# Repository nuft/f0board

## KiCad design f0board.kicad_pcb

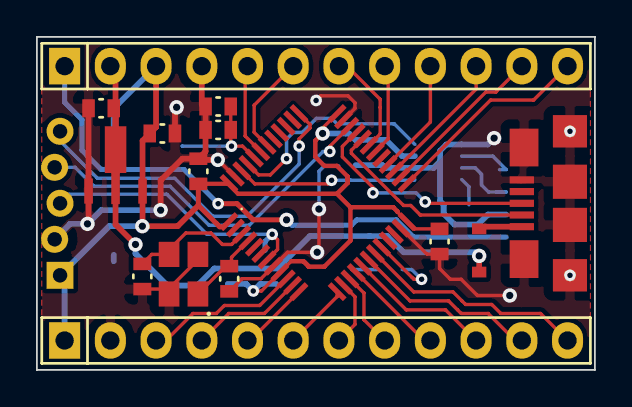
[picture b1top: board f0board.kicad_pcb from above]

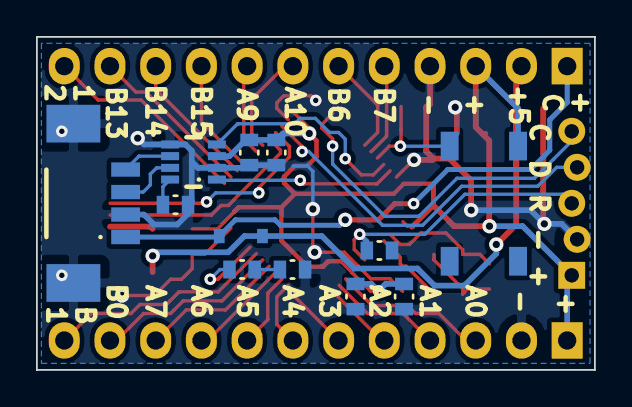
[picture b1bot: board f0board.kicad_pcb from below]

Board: 2 copper layers, 31.0 x 18.5 mm, 28 parts (12 on the bottom side), 38 nets.

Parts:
C1, C3, C4, C5, C7: 100nF; _0603
C2: 4.7uF; _0603
C6, C11, C12: 1uF; _0603
C8: 10nF; _0603
C9, C10: C; _0603
CONN1: SWD; _Pin2mm_5z
CONN2: CAN; _Molex-PicoBlade-SMD-4
CONN3: MICRO_USB; _Micro-USB-AB-receptacle-SMT
D1: LED; _0603
D2, D3: BAT60JFILM; _SOD-323
P1, P2: CONN_12; Pin_Header_Straight_1x12
R1: R; _0603
R2: 10k; _0603
R3: 0; _0603
SW1: SW_PUSH; _PTS525SK15-SMT-Pushbutton
U1: STM32F303CCT6; _LQFP48
U2: MCP1700; _MCP1700-SOT-89
U3: MAX3051; _SOT23-8
X1: XTAL-SMD-4-PADS; _TSX-3225-SMD-XTAL

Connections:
/5V: C11.1, D2.2, D3.2, P1.2, U2.3
/5VCAN: CONN2.1, D3.1, P1.1
/BOOT0: C1.1, R2.1, SW1.1, U1.44
/CAN_RX: U1.45, U3.4
/CAN_TX: U1.46, U3.1
/LED: D1.1, U1.20
/PA0: P2.3, U1.10
/PA1: P2.4, U1.11
/PA2: P2.5, U1.12
/PA3: P2.6, U1.13
/PA4: P2.7, U1.14
/PA5: P2.8, U1.15
/PA6: P2.9, U1.16
/PA7: P2.10, U1.17
/PA9: P1.8, U1.30
/PA10: P1.7, U1.31
/PB0: P2.11, U1.18
/PB1: P2.12, U1.19
/PB6: P1.6, U1.42
/PB7: P1.5, U1.43
/PB12: P1.12, U1.25
/PB13: P1.11, U1.26
/PB14: P1.10, U1.27
/PB15: P1.9, U1.28
/RST: C4.1, CONN1.3, U1.7
/SWDCLK: CONN1.5, U1.37
/SWDIO: CONN1.4, U1.34
/USB_DM: CONN3.2, U1.32
/USB_DP: CONN3.3, U1.33
/VUSB: CONN3.1, D2.1
GND: C1.2, C2.2, C3.2, C4.2, C5.2, C6.2, C7.2, C8.2, C9.2, C10.2, C11.2, C12.2, CONN1.2, CONN2.2, CONN2.MECH, CONN3.5, CONN3.6, P1.4, P2.2, R1.2, R2.2, R3.2, U1.8, U1.23, U1.35, U1.47, U2.1, U3.2, U3.5, X1.2, X1.4
unnamed: C9.1, U1.4, X1.1
unnamed: C10.1, U1.3, X1.3
unnamed: CONN2.3, U3.7
unnamed: CONN2.4, U3.6
unnamed: D1.2, R1.1
unnamed: R3.1, U3.8
VCC: C2.1, C3.1, C5.1, C6.1, C7.1, C8.1, C12.1, CONN1.1, P1.3, P2.1, SW1.2, U1.1, U1.9, U1.24, U1.36, U1.48, U2.2, U3.3

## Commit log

2014-12-07 Initial commit, schematic already done by @Stapelzeiger.
2014-12-07 Add annotation.
2014-12-07 Update lib, change settings.
2014-12-07 Create pcb file, started coarse placing, defined outline.
2014-12-07 Add dimensioning.
2014-12-07 placing/routing, change pinorder, add diode.
2014-12-09 Routing, change LED Pin.
2014-12-09 Change MCP1700 footprint.
2014-12-09 Big layout change, routing almost finished.
2014-12-09 Add missing connection to LED, improved GND and VCC routing.
2014-12-09 Improve GND connection.
2014-12-09 Connect USB shield to GND, update footprints to fix DRC issue.
2014-12-09 Changes at Crystal after review, improved GND connection.
2014-12-10 Additional GND via.
2014-12-10 Place board near to origin.
2014-12-10 Hide reference text in silkscreen.
2014-12-10 GND connection.
2014-12-10 inch grid alignment.
2014-12-10 Move LED for silkscreen.
2014-12-10 Move more compontents for silkscreen
2014-12-10 Begin with silkscreen pin tags, some space problems.
2014-12-10 Move pads for silkscreen.
2014-12-10 Change dimmension to nicer mm values.
